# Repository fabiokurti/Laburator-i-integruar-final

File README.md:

🧪 STM32F1 Embedded Systems Assignments
This repository contains schematic-based embedded system projects using STM32 microcontrollers. Each student is assigned a unique sensor module to integrate with an STM32, applying their knowledge in sensor interfacing and system design.

📋 Project Overview
Microcontroller: STM32F103C8T6TR

Design Platforms: STM32CubeIDE, KiCad v6+

Communication Protocols: I2C, SPI, UART (depends on assigned sensor)

Each student is expected to complete the following steps:

🔧 Project Instructions
1. Schematic Review
Navigate to your assigned project folder.

Examine the included schematic diagram.

Use only the sensor shown in the schematic.

Interface the sensor with the STM32 using the correct communication protocol (I2C, SPI, UART, analog, or digital).

2. Library Setup
Each project folder includes the symbol and footprint for the sensor.

Ensure you import these into KiCad.

3. Schematic Design
Connect the sensor to the STM32 in STM32CubeMX.

Select the appropriate pins based on the protocol.

4. PCB Layout
Convert your schematic to a PCB layout.

Follow the correct board stackup depending on the project:

4-Layer Stackup:

Top: Signal

Layer 2: VCC

Layer 3: GND

Bottom: Signal

2-Layer Stackup:

Top: Signal

Bottom: GND

5. Design Rules
VCC traces: 0.3 mm

Signal traces: 0.15 mm

Via size: 0.6 mm (outer) / 0.3 mm (inner)

✅ Learning Objectives
Practice sensor interfacing with STM32 microcontrollers

Design and demonstrate a functional embedded system project

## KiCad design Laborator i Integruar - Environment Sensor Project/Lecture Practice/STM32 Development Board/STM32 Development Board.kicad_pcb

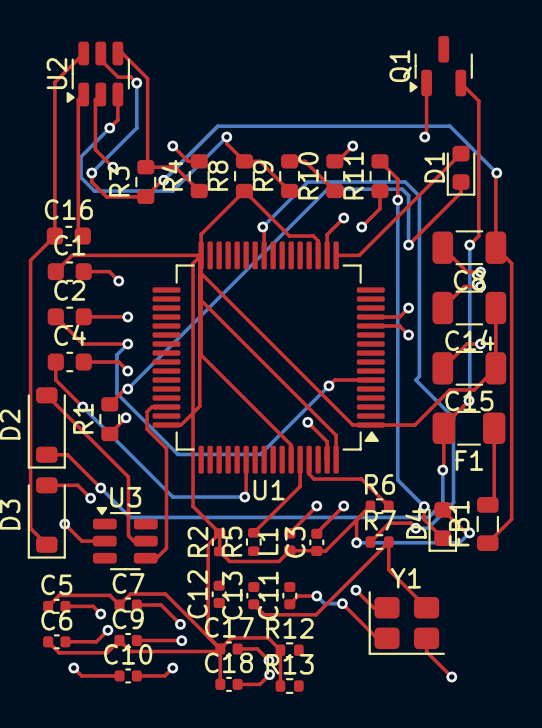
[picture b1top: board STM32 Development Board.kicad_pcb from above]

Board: 4 copper layers, 43 parts (0 on the bottom side), 23 nets.

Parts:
C1: 4u7; C_0603_1608Metric
C2, C4: 2u2; C_0603_1608Metric
C3, C5, C6, C7, C9: 100n; C_0402_1005Metric
C8, C14, C15: 10u; C_1206_3216Metric
C10: 1u; C_0402_1005Metric
C11, C13: 12p; C_0402_1005Metric
C12, C17, C18: 10n; C_0402_1005Metric
C16: 10n; C_0603_1608Metric
D1: BLUE; LED_0603_1608Metric
D2, D3: B5819W; D_SOD-123
D4: RED; LED_0603_1608Metric
F1: 250mA; Fuse_1206_3216Metric
FB1: 600 @ 600MHz; L_0805_2012Metric
L1: 39n; L_0402_1005Metric
Q1: AO3401A; SOT-23
R1: 1k5; R_0603_1608Metric
R2, R6, R12, R13: 2k2; R_0402_1005Metric
R3: 100k; R_0603_1608Metric
R4: 68k; R_0603_1608Metric
R5: 10k; R_0402_1005Metric
R7: 47; R_0402_1005Metric
R8: 47k; R_0603_1608Metric
R9: 15k; R_0603_1608Metric
R10: 270; R_0603_1608Metric
R11: 1k; R_0603_1608Metric
U1: STM32F405RGT6; LQFP-64_10x10mm_P0.5mm
U2: MP2359DJ-LF-Z; SOT-23-6
U3: USBLC6-2SC6; SOT-23-6
Y1: 16MHz; Crystal_SMD_3225-4Pin_3.2x2.5mm

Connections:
+3.3VA: C10.1, C12.1, L1.2, U1.13 (VDDA)
+5V: D2.2 (A), U3.5 (VBUS)
BOOT0: R5.2, U1.60 (BOOT0)
BUCK_BST: C16.2, U2.1 (BST)
BUCK_EN: R3.2, R4.1, U2.4 (EN)
BUCK_FB: R8.2, R9.1, U2.3 (FB)
BUCK_IN: C8.1, FB1.1, R3.1, U2.5 (IN)
BUCK_SW: C16.1, D3.1 (K), U2.6 (SW)
GND: C1.2, C2.2, C3.2, C4.2, C5.2, C6.2, C7.2, C8.2, C9.2, C10.2, C11.2, C12.2, C13.2, C14.2, C15.2, C17.2, C18.2, D3.2 (A), Q1.1 (G), R1.1, R4.2, R10.2, R11.1, U1.12 (VSSA), U1.18 (VSS), U1.63 (VSS), U2.2 (GND), U3.2 (GND), Y1.2, Y1.4
HSE_IN: C11.1, U1.24 (PC4), Y1.1
HSE_OUT: R7.1, U1.25 (PC5)
I2C1_SCL: C1.1, C3.1, C5.1, C6.1, C7.1, C9.1, C14.1, C15.1, C17.1, C18.1, D4.2 (A), L1.1, R2.1, R2.2, R6.1, R8.1, R12.1, R13.1, U1.1 (VBAT), U1.19 (VDD), U1.32 (VDD), U1.48 (VDD), U1.59 (PB7), U1.64 (VDD)
I2C1_SDA: R6.2, U1.61 (PB8)
LED_STATUS: D1.2 (A), U1.17 (PA3)
unnamed: C13.1, R7.2, Y1.3
unnamed: D1.1 (K), R1.2
unnamed: D2.1 (K), F1.2, Q1.2 (S)
unnamed: D4.1 (K), R11.2
unnamed: F1.1, FB1.2
unnamed: R9.2, R10.1
unnamed: C4.1, U1.54 (PD2)
unnamed: C2.1, U1.6 (PH1)
USB_D_P: U1.46 (PA13), U3.4 (I/O2)

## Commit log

2025-06-12 readme
2025-06-12 done
